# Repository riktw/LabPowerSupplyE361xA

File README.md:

# LabPowerSupplyE361xA
A E3611A based lab power supply with digital controls

More info on the corresponding [blog post.](https://justanotherelectronicsblog.com/?p=846)

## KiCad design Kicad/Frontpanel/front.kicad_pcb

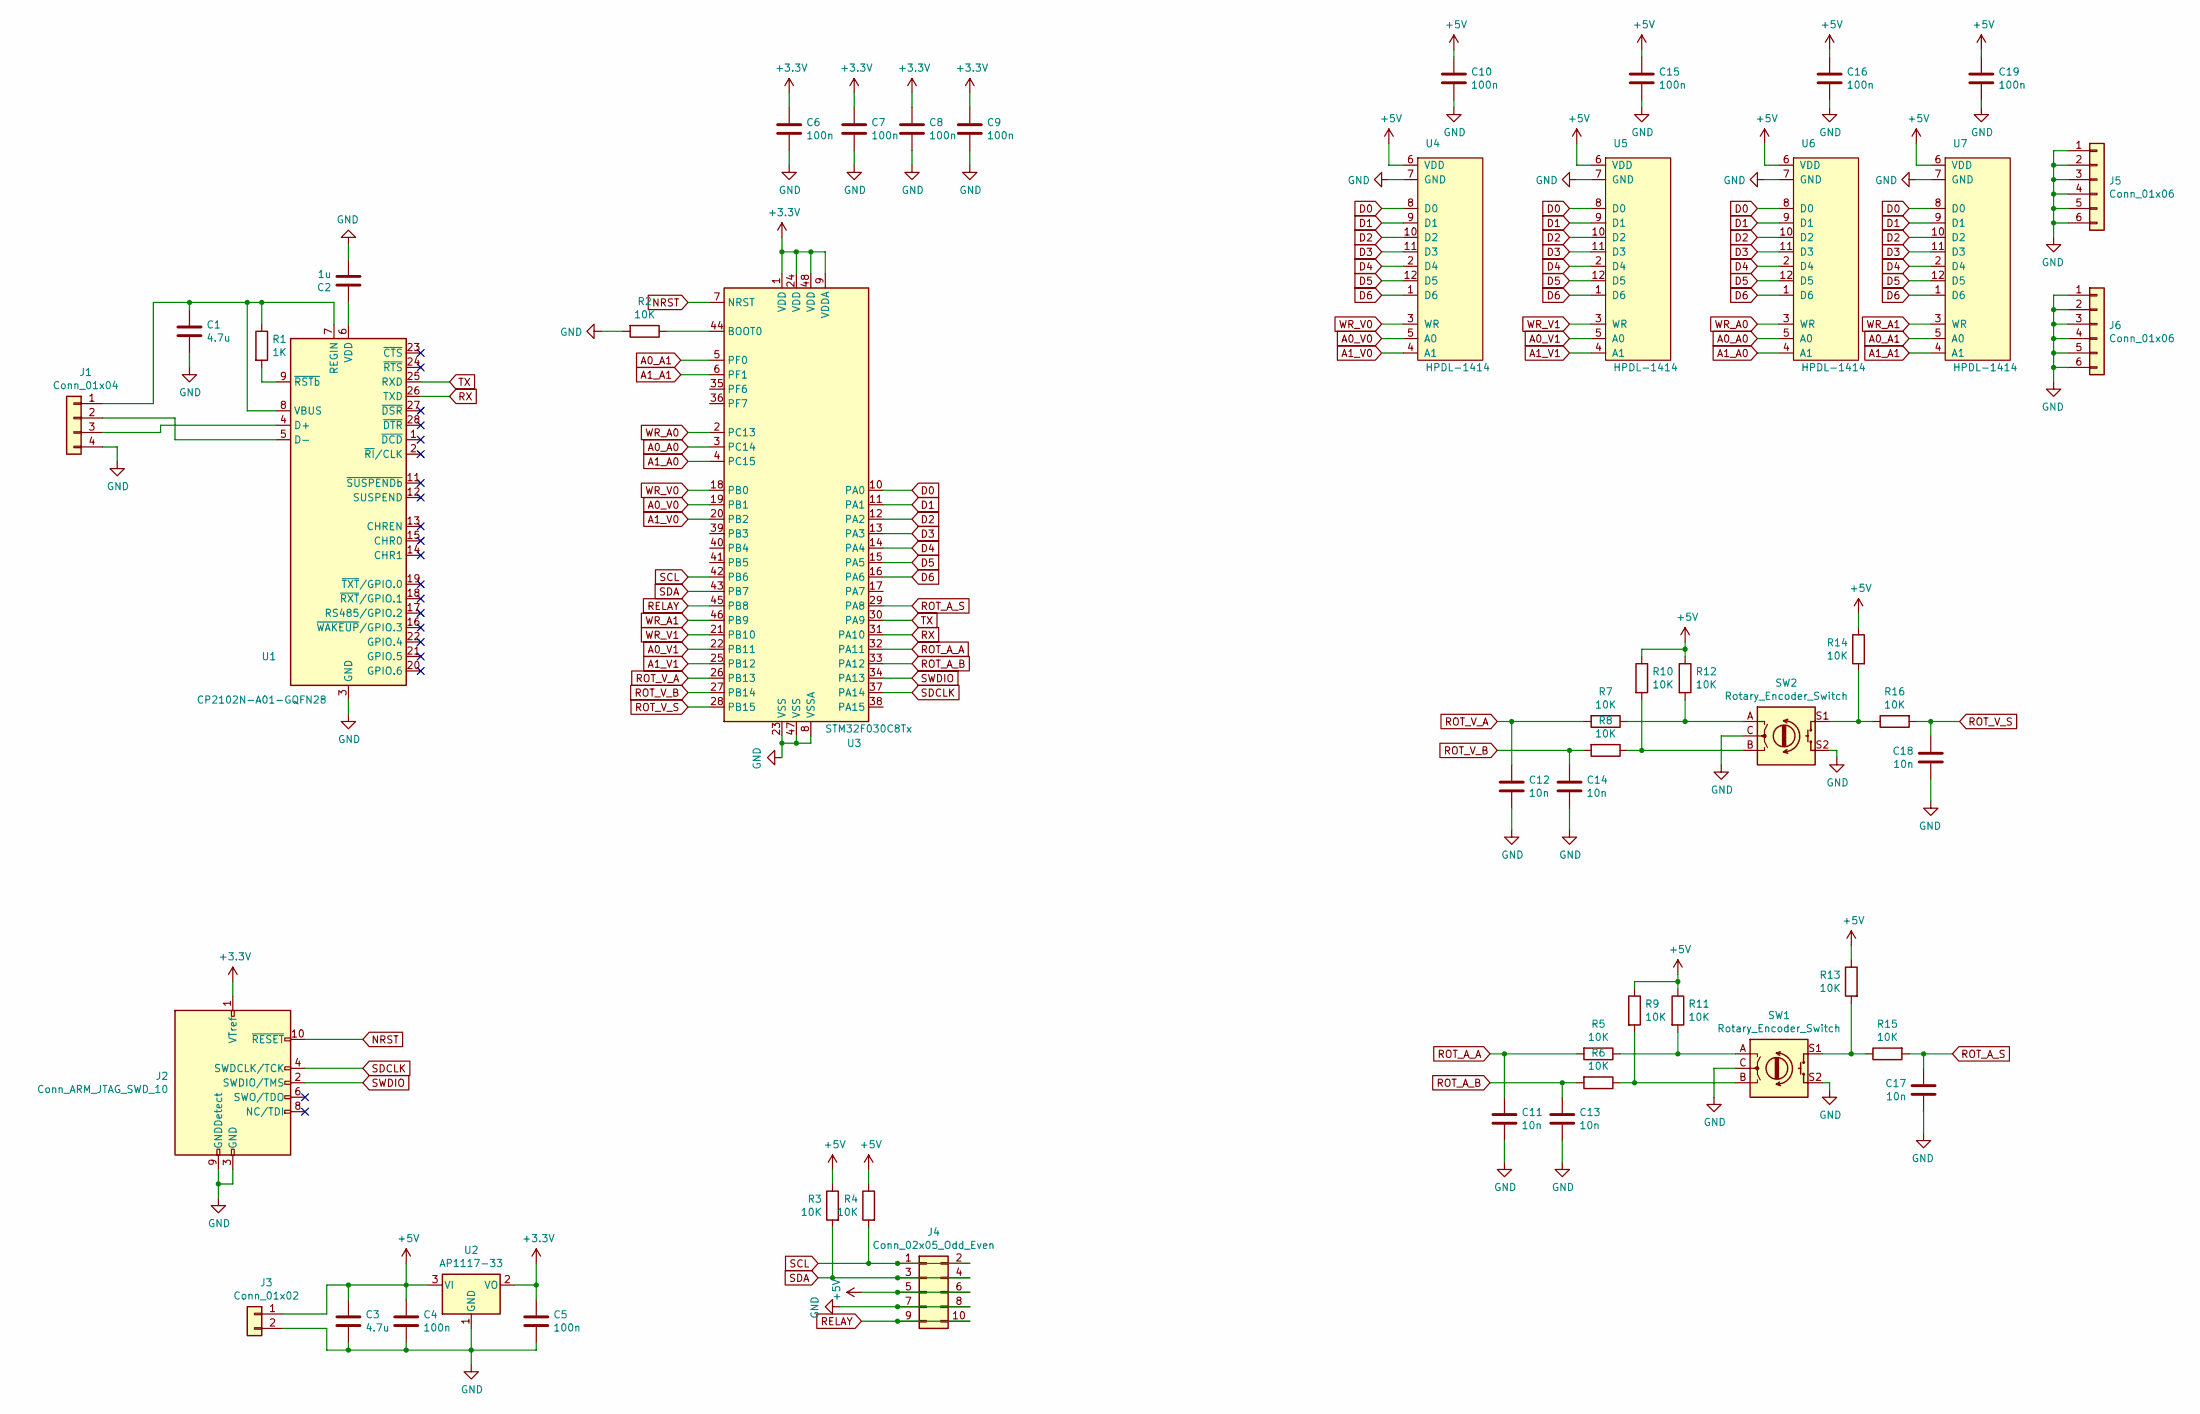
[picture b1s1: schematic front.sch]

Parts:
C1, C3: 4.7u; C_0603_1608Metric_Pad1.05x0.95mm_HandSolder
C2: 1u; C_0603_1608Metric_Pad1.05x0.95mm_HandSolder
C4, C5, C6, C7, C8, C9, C10, C15, C16, C19: 100n; C_0603_1608Metric_Pad1.05x0.95mm_HandSolder
C11, C12, C13, C14, C17, C18: 10n; C_0603_1608Metric_Pad1.05x0.95mm_HandSolder
J1: Conn_01x04; PinHeader_1x04_P2.54mm_Vertical
J2: Conn_ARM_JTAG_SWD_10; PinHeader_2x05_P1.27mm_Vertical_SMD
J3: Conn_01x02; Wago_734-132_1x02_P3.50mm_Vertical
J4: Conn_02x05_Odd_Even; IDC-Header_2x05_P2.54mm_Vertical
J5, J6: Conn_01x06; PinSocket_1x06_P2.54mm_Vertical
R1: 1K; R_0603_1608Metric_Pad1.05x0.95mm_HandSolder
R2, R3, R4, R5, R6, R7, R8, R9, R10, R11, R12, R13, R14, R15, R16: 10K; R_0603_1608Metric_Pad1.05x0.95mm_HandSolder
SW1, SW2: Rotary_Encoder_Switch; RotaryEncoder_Alps_EC11E-Switch_Vertical_H20mm
U1: CP2102N-A01-GQFN28; QFN-28-1EP_5x5mm_P0.5mm_EP3.35x3.35mm; JLC C6568
U2: AP1117-33; SOT-223-3_TabPin2
U3: STM32F030C8Tx; LQFP-48_7x7mm_P0.5mm
U4, U5, U6, U7: HPDL-1414

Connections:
+3V3: C5.1, C6.1, C7.1, C8.1, C9.1, J2.1 (VTref), U2.2 (VO), U3.1 (VDD), U3.9 (VDDA), U3.24 (VDD), U3.48 (VDD)
+5V: C3.1, C4.1, C10.1, C15.1, C16.1, C19.1, J3.1, J4.5, J4.6, R3.1, R4.1, R9.1, R10.1, R11.1, R12.1, R13.1, R14.1, U2.3 (VI), U4.6 (VDD), U5.6 (VDD), U6.6 (VDD), U7.6 (VDD)
A0_A0: U3.3 (PC14), U6.5 (A0)
A0_A1: U3.5 (PF0), U7.5 (A0)
A0_V0: U3.19 (PB1), U4.5 (A0)
A0_V1: U3.22 (PB11), U5.5 (A0)
A1_A0: U3.4 (PC15), U6.4 (A1)
A1_A1: U3.6 (PF1), U7.4 (A1)
A1_V0: U3.20 (PB2), U4.4 (A1)
A1_V1: U3.25 (PB12), U5.4 (A1)
D0: U3.10 (PA0), U4.8 (D0), U5.8 (D0), U6.8 (D0), U7.8 (D0)
D1: U3.11 (PA1), U4.9 (D1), U5.9 (D1), U6.9 (D1), U7.9 (D1)
D2: U3.12 (PA2), U4.10 (D2), U5.10 (D2), U6.10 (D2), U7.10 (D2)
D3: U3.13 (PA3), U4.11 (D3), U5.11 (D3), U6.11 (D3), U7.11 (D3)
D4: U3.14 (PA4), U4.2 (D4), U5.2 (D4), U6.2 (D4), U7.2 (D4)
D5: U3.15 (PA5), U4.12 (D5), U5.12 (D5), U6.12 (D5), U7.12 (D5)
D6: U3.16 (PA6), U4.1 (D6), U5.1 (D6), U6.1 (D6), U7.1 (D6)
GND: C1.2, C2.2, C3.2, C4.2, C5.2, C6.2, C7.2, C8.2, C9.2, C10.2, C11.2, C12.2, C13.2, C14.2, C15.2, C16.2, C17.2, C18.2, C19.2, J1.4, J2.3 (GND), J2.5 (GND), J2.9 (GNDDetect), J3.2, J4.7, J4.8, J5.1, J5.2, J5.3, J5.4, J5.5, J5.6, J6.1, J6.2, J6.3, J6.4, J6.5, J6.6, R2.2, SW1.C, SW1.S2, SW2.C, SW2.S2, U1.3 (GND), U1.29 (GND), U2.1 (GND), U3.8 (VSSA), U3.23 (VSS), U3.47 (VSS), U4.7 (GND), U5.7 (GND), U6.7 (GND), U7.7 (GND)
NRST: J2.10 (~RESET~), U3.7 (NRST)
unnamed: C1.1, J1.1, R1.1, U1.7 (REGIN), U1.8 (VBUS)
unnamed: C2.1, U1.6 (VDD)
unnamed: J1.2, U1.5 (D-)
unnamed: J1.3, U1.4 (D+)
unnamed: R1.2, U1.9 (~RSTb)
unnamed: R2.1, U3.44 (BOOT0)
unnamed: R6.1, R9.2, SW1.B
unnamed: R8.1, R10.2, SW2.B
unnamed: R5.1, R11.2, SW1.A
unnamed: R7.1, R12.2, SW2.A
unnamed: R13.2, R15.1, SW1.S1
unnamed: R14.2, R16.1, SW2.S1
RELAY: J4.9, J4.10, U3.45 (PB8)
ROT_A_A: C11.1, R5.2, U3.32 (PA11)
ROT_A_B: C13.1, R6.2, U3.33 (PA12)
ROT_A_S: C17.1, R15.2, U3.29 (PA8)
ROT_V_A: C12.1, R7.2, U3.26 (PB13)
ROT_V_B: C14.1, R8.2, U3.27 (PB14)
ROT_V_S: C18.1, R16.2, U3.28 (PB15)
RX: U1.26 (TXD), U3.31 (PA10)
SCL: J4.1, J4.2, R4.2, U3.42 (PB6)
SDA: J4.3, J4.4, R3.2, U3.43 (PB7)
SDCLK: J2.4 (SWDCLK/TCK), U3.37 (PA14)
SWDIO: J2.2 (SWDIO/TMS), U3.34 (PA13)
TX: U1.25 (RXD), U3.30 (PA9)
WR_A0: U3.2 (PC13), U6.3 (WR)
WR_A1: U3.46 (PB9), U7.3 (WR)
WR_V0: U3.18 (PB0), U4.3 (WR)
WR_V1: U3.21 (PB10), U5.3 (WR)

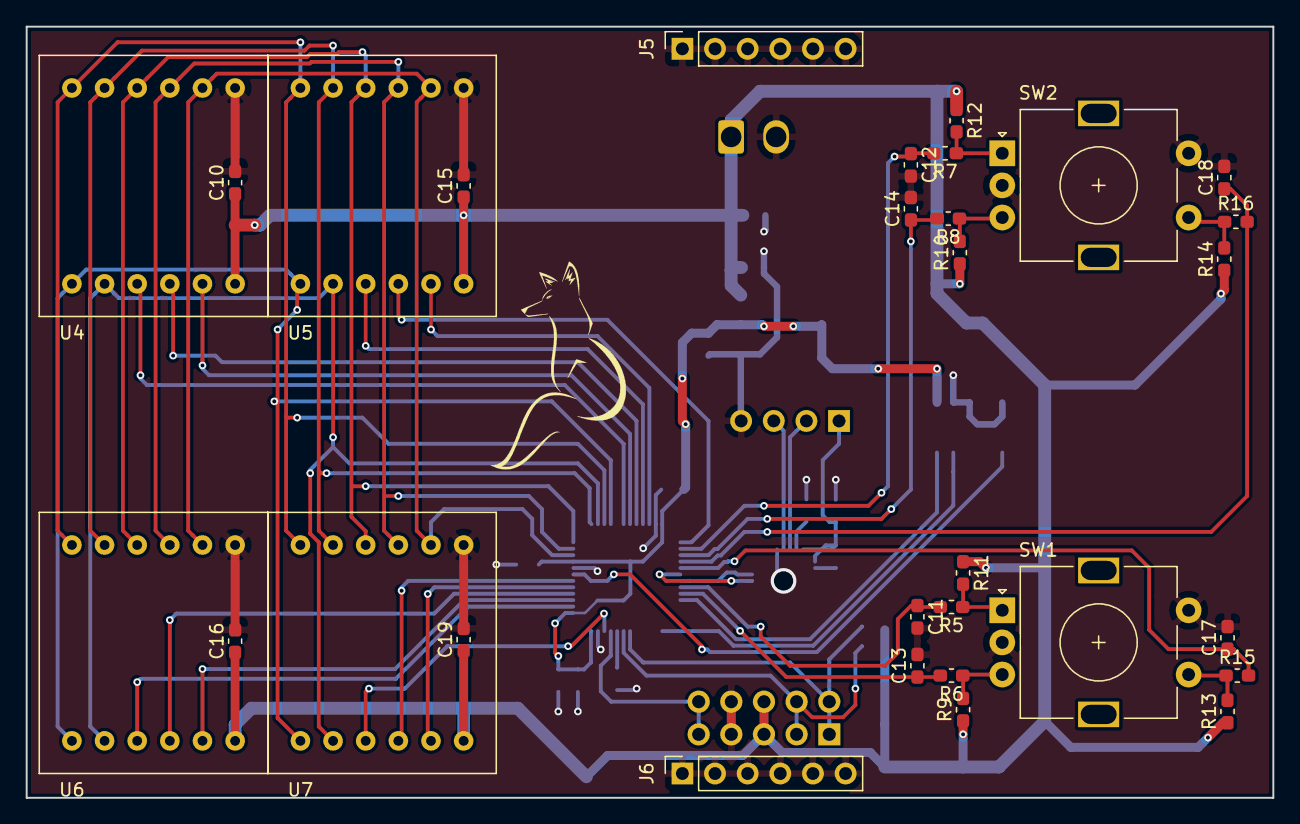
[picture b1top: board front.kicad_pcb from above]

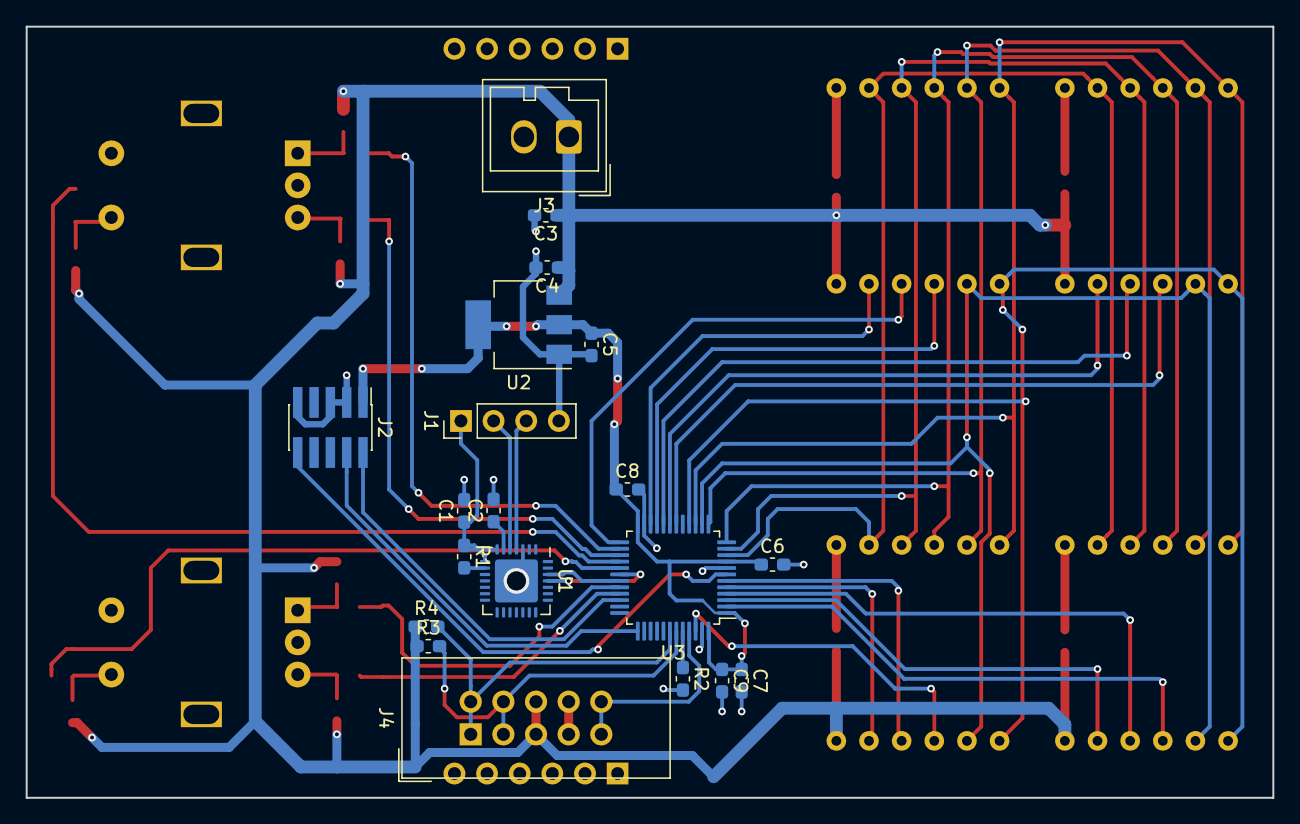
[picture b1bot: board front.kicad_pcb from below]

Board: 2 copper layers, 97.0 x 60.0 mm, 50 parts (20 on the bottom side), 48 nets.

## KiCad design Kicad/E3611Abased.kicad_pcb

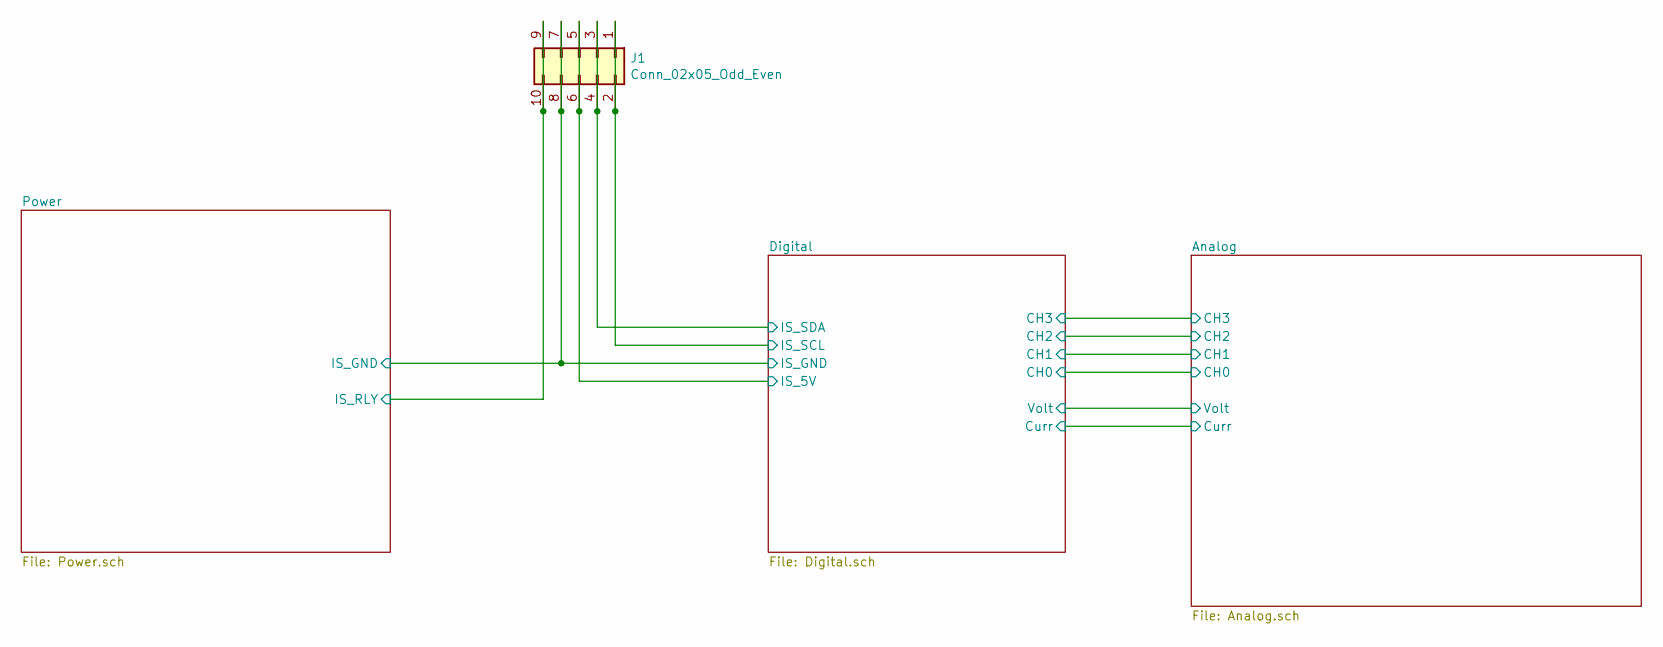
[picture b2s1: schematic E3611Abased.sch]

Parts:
J1: Conn_02x05_Odd_Even; IDC-Header_2x05_P2.54mm_Vertical

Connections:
/Digital/IS_5V: J1.5, J1.6; also elsewhere on the board
/Digital/IS_GND: J1.7, J1.8; also elsewhere on the board
/Digital/IS_SCL: J1.1, J1.2; also elsewhere on the board
/Digital/IS_SDA: J1.3, J1.4; also elsewhere on the board
/Power/IS_RLY: J1.9, J1.10; also elsewhere on the board

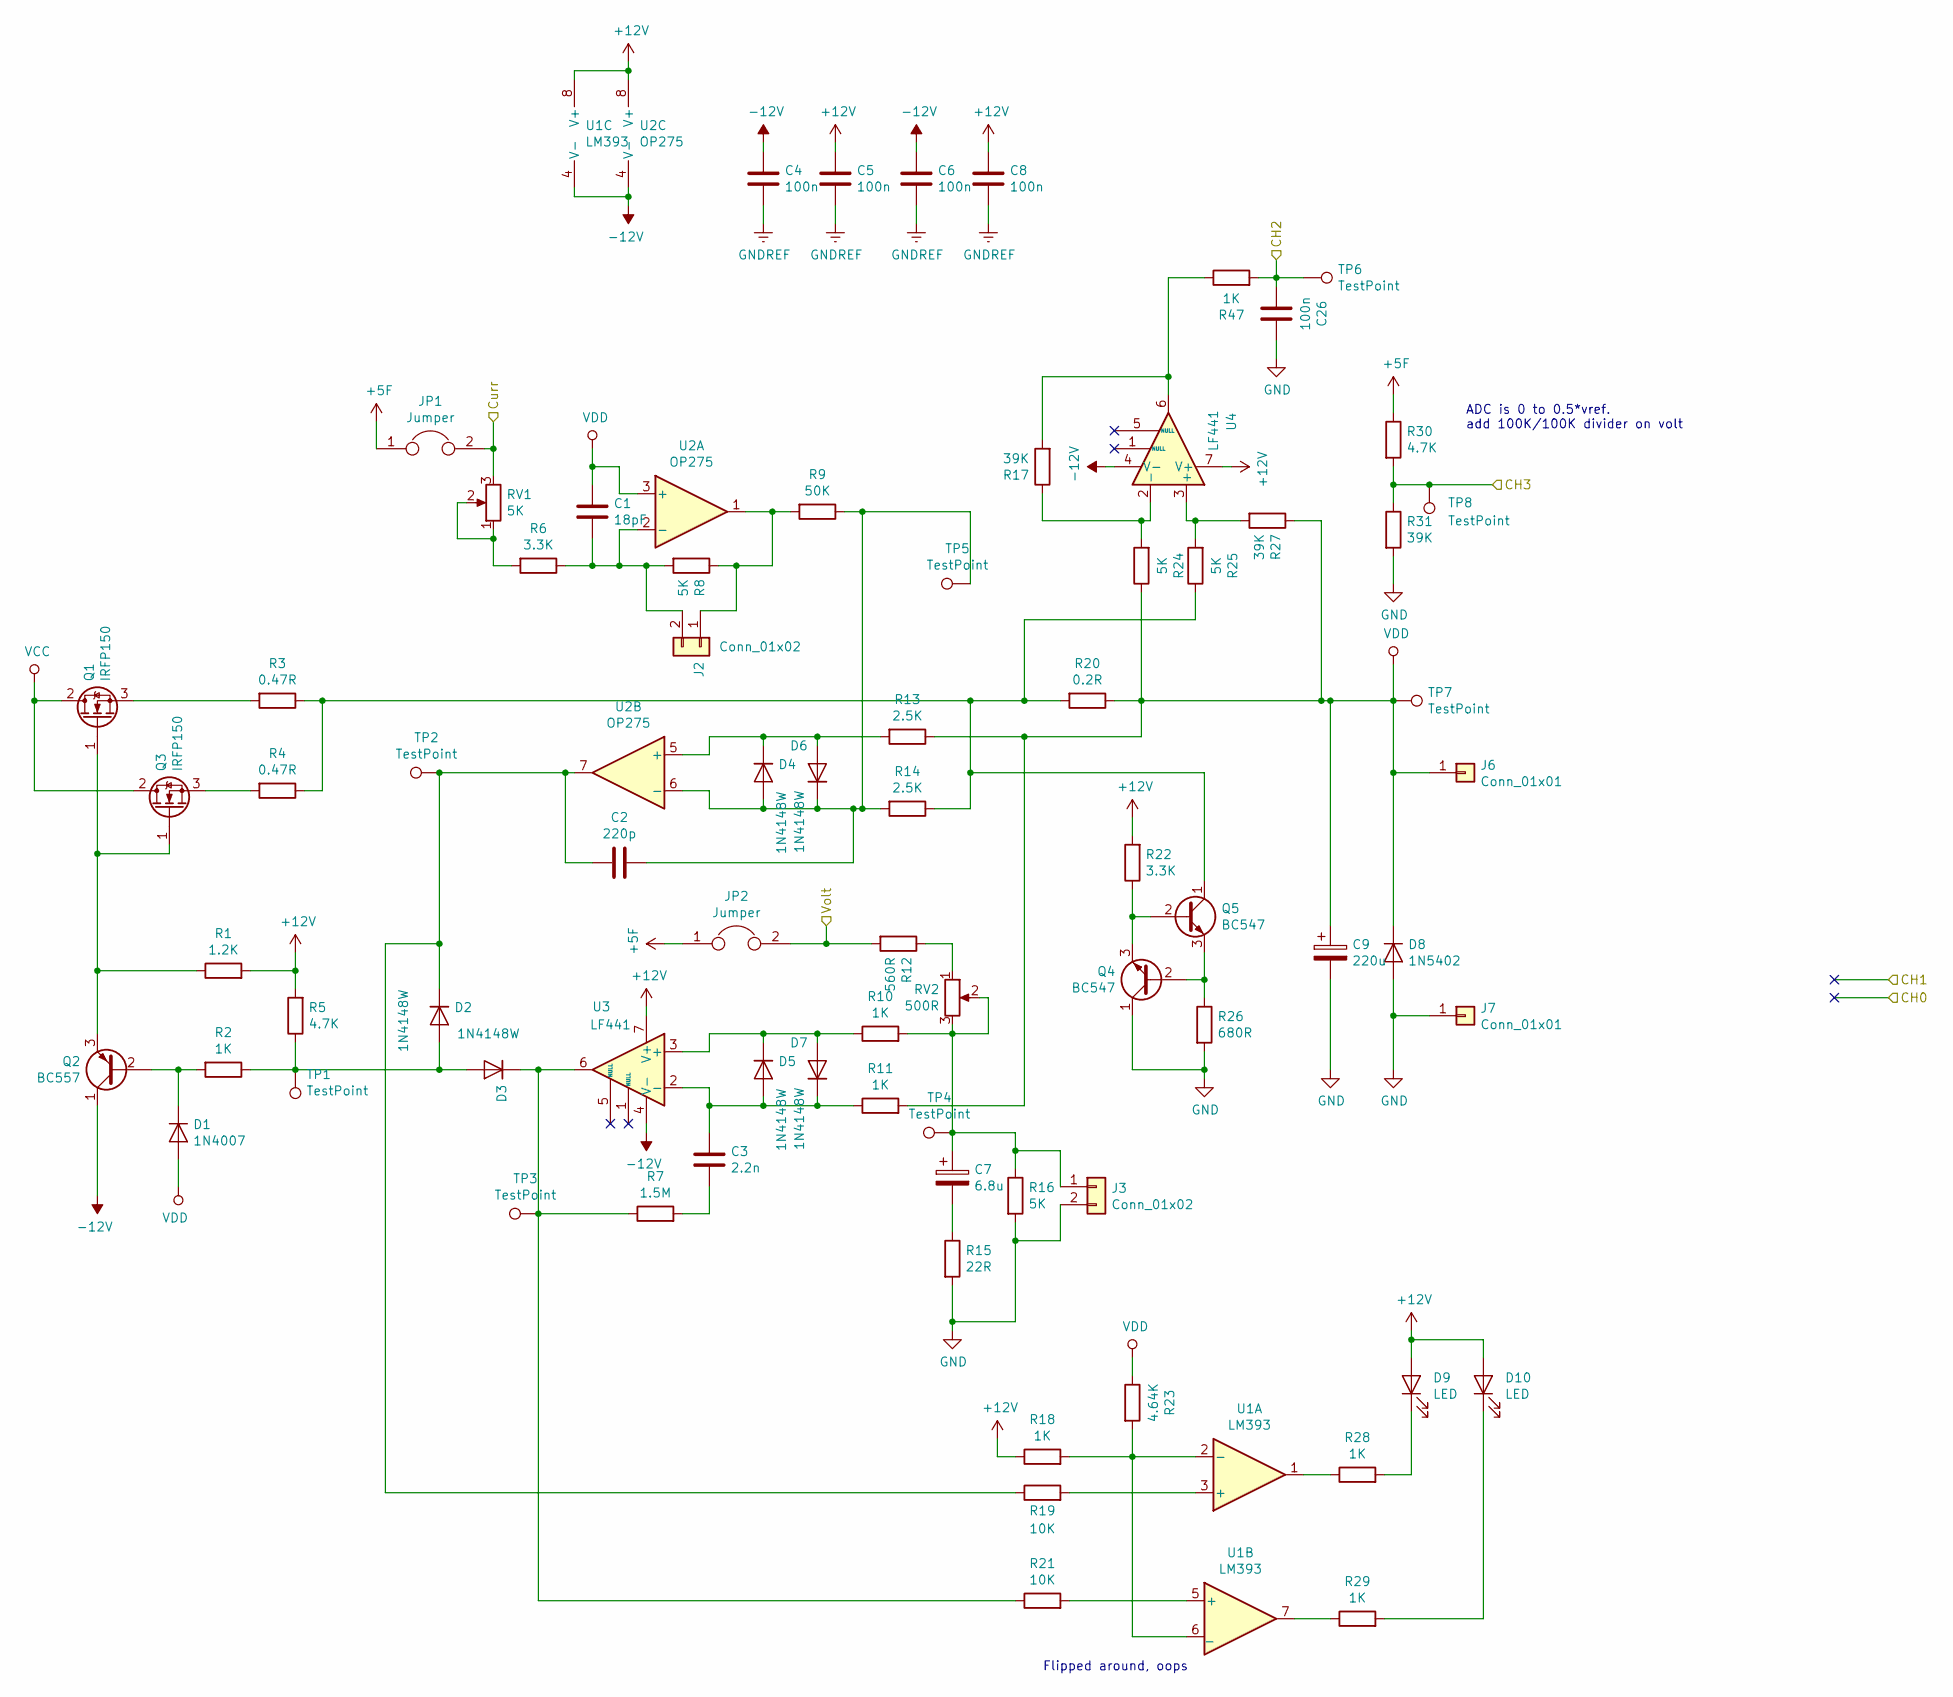
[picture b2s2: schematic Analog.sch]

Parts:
C1: 18pF; C_0603_1608Metric_Pad1.05x0.95mm_HandSolder
C2: 220p; C_0603_1608Metric_Pad1.05x0.95mm_HandSolder
C3: 2.2n; C_0603_1608Metric_Pad1.05x0.95mm_HandSolder
C4, C5, C6, C8, C26: 100n; C_0603_1608Metric_Pad1.05x0.95mm_HandSolder
C7: 6.8u; CP_Elec_6.3x3
C9: 220u; CP_Radial_D10.0mm_P5.00mm
D1: 1N4007; D_DO-41_SOD81_P10.16mm_Horizontal
D2, D3, D4, D5, D6, D7: 1N4148W; D_SOD-123
D8: 1N5402; D_DO-201AD_P15.24mm_Horizontal
D9, D10: LED; LED_D5.0mm
J2, J3: Conn_01x02; TerminalBlock_Phoenix_MKDS-1,5-2-5.08_1x02_P5.08mm_Horizont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
J6, J7: Conn_01x01; 24.243_Banana_plug
JP1, JP2: Jumper; SolderJumper-2_P1.3mm_Open_Pad1.0x1.5mm
Q1, Q3: IRFP150; TO-247-3_Vertical
Q2: BC557; TO-92_Inline
Q4, Q5: BC547; TO-92_Inline
R1: 1.2K; R_0603_1608Metric_Pad1.05x0.95mm_HandSolder
R2, R10, R11, R18, R28, R29, R47: 1K; R_0603_1608Metric_Pad1.05x0.95mm_HandSolder
R3, R4: 0.47R; R_Axial_DIN0207_L6.3mm_D2.5mm_P15.24mm_Horizontal
R5, R30: 4.7K; R_0603_1608Metric_Pad1.05x0.95mm_HandSolder
R6, R22: 3.3K; R_0603_1608Metric_Pad1.05x0.95mm_HandSolder
R7: 1.5M; R_0603_1608Metric_Pad1.05x0.95mm_HandSolder
R8, R16, R24, R25: 5K; R_0603_1608Metric_Pad1.05x0.95mm_HandSolder
R9: 50K; R_0603_1608Metric_Pad1.05x0.95mm_HandSolder
R12: 560R; R_0603_1608Metric_Pad1.05x0.95mm_HandSolder
R13, R14: 2.5K; R_0603_1608Metric_Pad1.05x0.95mm_HandSolder
R15: 22R; R_0603_1608Metric_Pad1.05x0.95mm_HandSolder
R17, R27, R31: 39K; R_0603_1608Metric_Pad1.05x0.95mm_HandSolder
R19, R21: 10K; R_0603_1608Metric_Pad1.05x0.95mm_HandSolder
R20: 0.2R; R_Axial_DIN0207_L6.3mm_D2.5mm_P15.24mm_Horizontal
R23: 4.64K; R_0603_1608Metric_Pad1.05x0.95mm_HandSolder
R26: 680R; R_0603_1608Metric_Pad1.05x0.95mm_HandSolder
RV1: 5K; Potentiometer_Bourns_3266Y_Vertical
RV2: 500R; Potentiometer_Bourns_3266Y_Vertical
TP1, TP2, TP3, TP4, TP5, TP6, TP7, TP8: TestPoint; TestPoint_Loop_D1.80mm_Drill1.0mm_Beaded
U1: LM393; SOIC-8_3.9x4.9mm_P1.27mm
U2: OP275; SOIC-8_3.9x4.9mm_P1.27mm
U3, U4: LF441; SOIC-8_3.9x4.9mm_P1.27mm

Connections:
+5F: JP1.1, JP2.1, R30.1; also elsewhere on the board
+12V: C5.1, C8.1, D9.2 (A), D10.2 (A), R1.2, R5.2, R18.1, R22.2, U1.8 (V+), U2.8 (V+), U3.7 (V+), U4.7 (V+); also elsewhere on the board
-12V: C4.1, C6.1, Q2.1 (C), U1.4 (V-), U2.4 (V-), U3.4 (V-), U4.4 (V-); also elsewhere on the board
/Analog/CH2: C26.2, R47.2, TP6.1; also elsewhere on the board
/Analog/CH3: R30.2, R31.1, TP8.1; also elsewhere on the board
/Analog/Curr: JP1.2, RV1.3; also elsewhere on the board
/Analog/Volt: JP2.2, R12.2; also elsewhere on the board
GND: C9.2, C26.1, D8.2 (A), J3.2, J7.1, Q4.1 (C), R15.2, R16.2, R26.2, R31.2; also elsewhere on the board
GNDREF: C1.1, C4.2, C5.2, C6.2, C8.2, C9.1, D1.2 (A), D8.1 (K), J6.1, R11.2, R13.1, R20.1, R23.1, R24.1, R27.1, TP7.1, U2.3 (+); also elsewhere on the board
unnamed: C1.2, J2.2, R6.1, R8.2, U2.2 (-)
unnamed: C2.1, D4.2 (A), D6.1 (K), R9.1, R14.2, TP5.1, U2.6 (-)
unnamed: C2.2, D2.1 (K), R19.1, TP2.1, U2.7
unnamed: C3.1, D5.2 (A), D7.1 (K), R11.1, U3.2 (-)
unnamed: C3.2, R7.2
unnamed: C7.1, J3.1, R10.2, R16.1, RV2.2, RV2.3, TP4.1
unnamed: C7.2, R15.1
unnamed: D1.1 (K), Q2.2 (B), R2.2
unnamed: D2.2 (A), D3.2 (A), R2.1, R5.1, TP1.1
unnamed: D3.1 (K), R7.1, R21.1, TP3.1, U3.6
unnamed: D4.1 (K), D6.2 (A), R13.2, U2.5 (+)
unnamed: D5.1 (K), D7.2 (A), R10.1, U3.3 (+)
unnamed: D9.1 (K), R28.2
unnamed: D10.1 (K), R29.2
unnamed: J2.1, R8.1, R9.2, U2.1
unnamed: Q1.1 (G), Q2.3 (E), Q3.1 (G), R1.1
unnamed: Q1.3 (S), R3.2
unnamed: Q3.3 (S), R4.2
unnamed: Q4.2 (B), Q5.3 (E), R26.1
unnamed: Q4.3 (E), Q5.2 (B), R22.1
unnamed: Q5.1 (C), R3.1, R4.1, R14.1, R20.2, R25.1
unnamed: R6.2, RV1.1, RV1.2
unnamed: R12.1, RV2.1
unnamed: R17.1, R24.2, U4.2 (-)
unnamed: R17.2, R47.1, U4.6
unnamed: R18.2, R23.2, U1.2 (-), U1.6 (_)
unnamed: R19.2, U1.3 (+)
unnamed: R21.2, U1.5 (+)
unnamed: R25.2, R27.2, U4.3 (+)
unnamed: R28.1, U1.1
unnamed: R29.1, U1.7
VCC: Q1.2 (D), Q3.2 (D); also elsewhere on the board

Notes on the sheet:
ADC is 0 to 0.5*vref. add 100K/100K divider on volt
Flipped around, oops

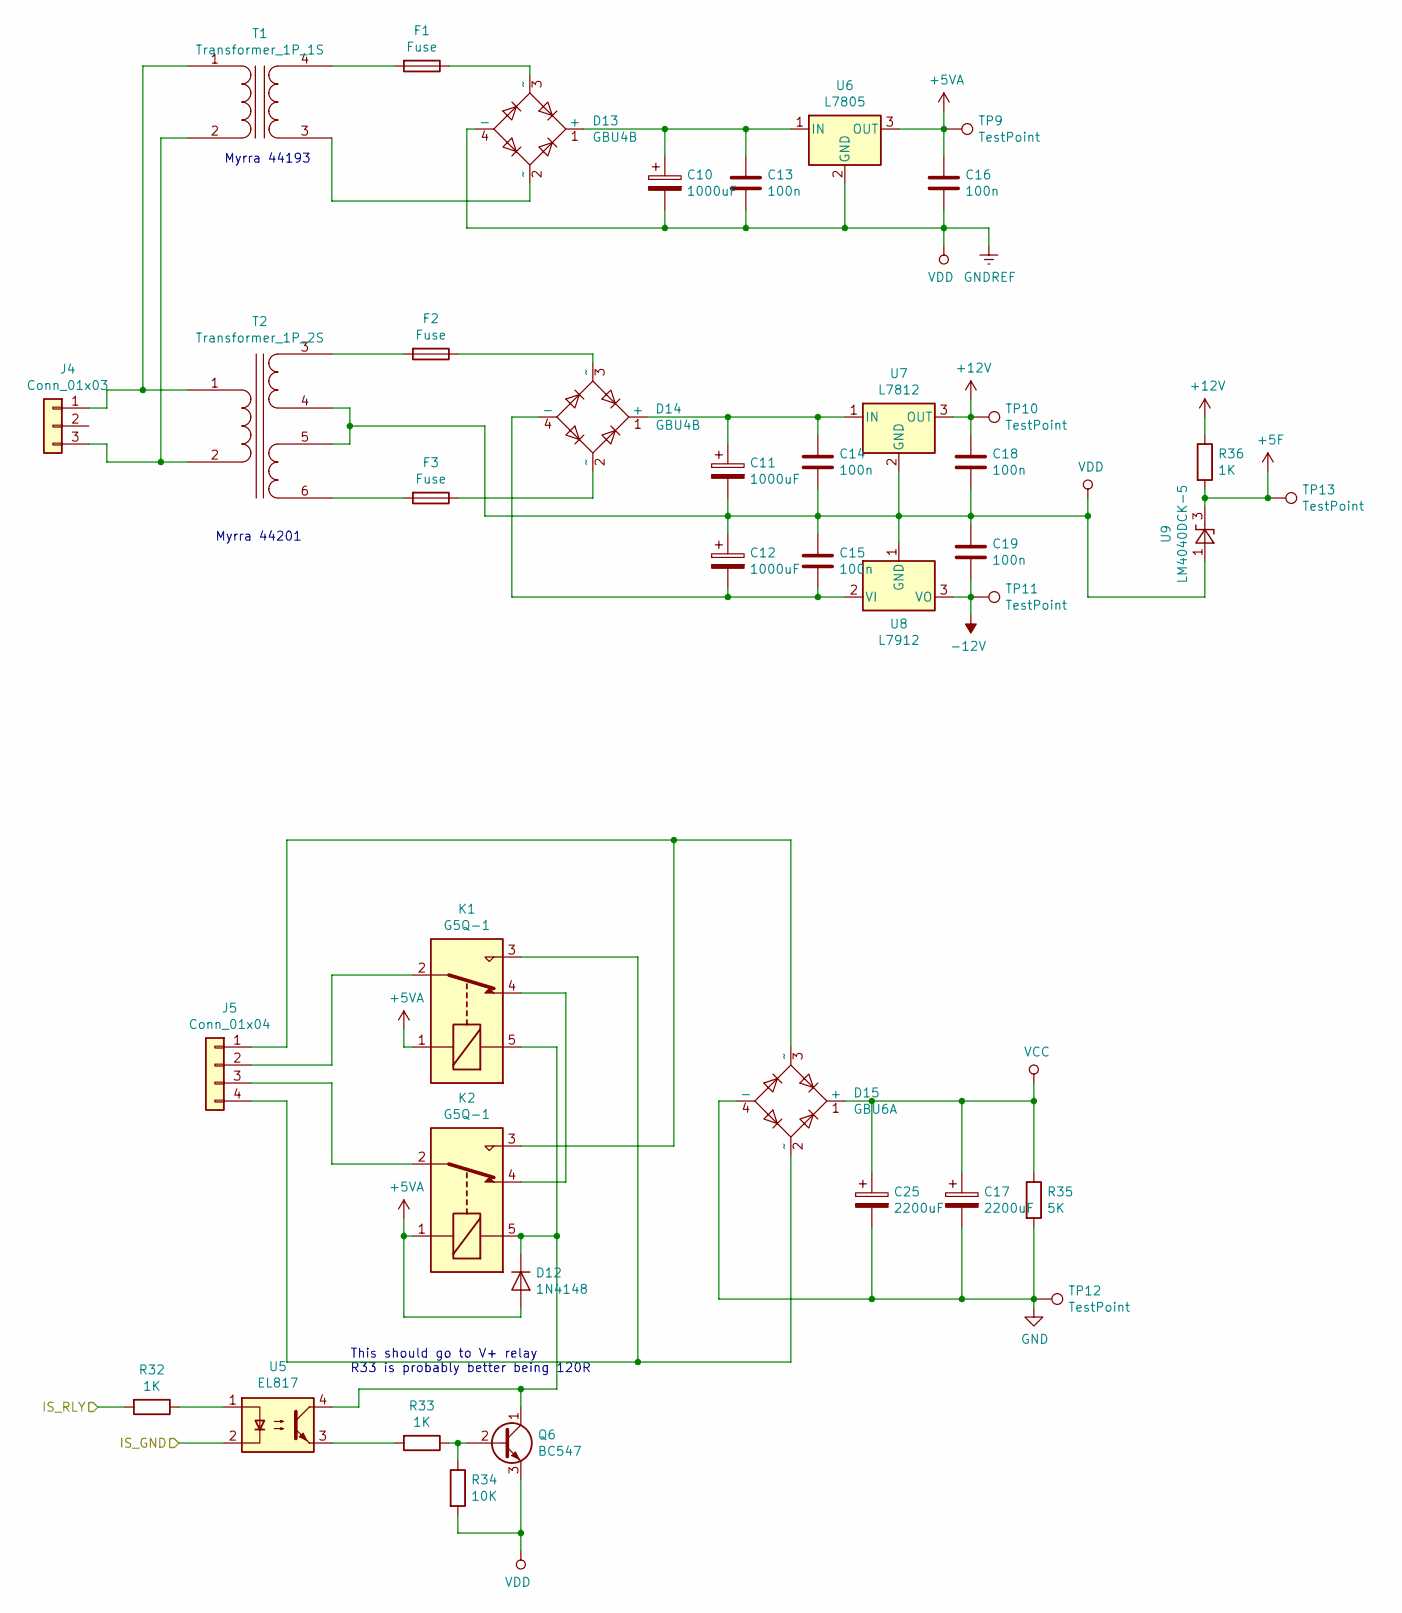
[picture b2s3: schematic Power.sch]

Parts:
C10, C11, C12: 1000uF; CP_Radial_D10.0mm_P5.00mm
C13, C14, C15, C16, C18, C19: 100n; C_Disc_D5.0mm_W2.5mm_P5.00mm
C17, C25: 2200uF; CP_Radial_D18.0mm_P7.50mm
D12: 1N4148; D_DO-35_SOD27_P7.62mm_Horizontal
D13, D14: GBU4B; Diode_Bridge_Vishay_GBU
D15: GBU6A; Diode_Bridge_Vishay_GBU
F1, F2, F3: Fuse; Fuseholder_Cylinder-5x20mm_Stelvio-Kontek_PTF78_Horizontal_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
J4: Conn_01x03; TerminalBlock_Phoenix_MKDS-1,5-3-5.08_1x03_P5.08mm_Horizont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
J5: Conn_01x04; TerminalBlock_Phoenix_MKDS-1,5-4-5.08_1x04_P5.08mm_Horizont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
K1, K2: G5Q-1; Relay_SPDT_Omron-G5Q-1
Q6: BC547; TO-92_Inline
R32, R33: 1K; R_0603_1608Metric_Pad1.05x0.95mm_HandSolder
R34: 10K; R_0603_1608Metric_Pad1.05x0.95mm_HandSolder
R35: 5K; R_Axial_DIN0414_L11.9mm_D4.5mm_P15.24mm_Horizontal
R36: 1K; R_0603_1608Metric
T1: Transformer_1P_1S; 44XXX_Transformer_3.2VA_Single
T2: Transformer_1P_2S; 44XXX_Transformer_3.2VA
TP9, TP10, TP11, TP12, TP13: TestPoint; TestPoint_Loop_D1.80mm_Drill1.0mm_Beaded
U5: EL817; DIP-4_W7.62mm
U6: L7805; TO-220-3_Vertical
U7: L7812; TO-220-3_Vertical
U8: L7912; TO-220-3_Vertical
U9: LM4040DCK-5; SOT-353_SC-70-5

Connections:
+5F: R36.2, TP13.1, U9.3 (K); also elsewhere on the board
+5VA: C16.1, D12.2 (A), K1.1, K2.1, TP9.1, U6.3 (OUT); also elsewhere on the board
+12V: C18.1, R36.1, TP10.1, U7.3 (OUT); also elsewhere on the board
-12V: C19.2, TP11.1, U8.3 (VO); also elsewhere on the board
/Digital/IS_GND: U5.2; also elsewhere on the board
/Power/IS_RLY: R32.2; also elsewhere on the board
GND: C17.2, C25.2, D15.4 (-), R35.2, TP12.1; also elsewhere on the board
GNDREF: C10.2, C11.2, C12.1, C13.2, C14.2, C15.1, C16.2, C18.2, C19.1, D13.4 (-), Q6.3 (E), R34.2, T2.4 (SB), T2.5 (SC), U6.2 (GND), U7.2 (GND), U8.1 (GND), U9.1 (A); also elsewhere on the board
unnamed: C10.1, C13.1, D13.1 (+), U6.1 (IN)
unnamed: C11.1, C14.1, D14.1 (+), U7.1 (IN)
unnamed: C12.2, C15.2, D14.4 (-), U8.2 (VI)
unnamed: D12.1 (K), K1.5, K2.5, Q6.1 (C), U5.4
unnamed: D13.2 (~~), T1.3 (SA)
unnamed: D13.3 (~~), F1.1
unnamed: D14.2 (~~), F3.1
unnamed: D14.3 (~~), F2.1
unnamed: D15.2 (~~), J5.4, K1.3
unnamed: D15.3 (~~), J5.1, K2.3
unnamed: F1.2, T1.4 (SB)
unnamed: F2.2, T2.3 (SA)
unnamed: F3.2, T2.6 (SD)
unnamed: J4.1, T1.1 (AA), T2.1 (AA)
unnamed: J4.3, T1.2 (AB), T2.2 (AB)
unnamed: J5.2, K1.2
unnamed: J5.3, K2.2
unnamed: K1.4, K2.4
unnamed: Q6.2 (B), R33.1, R34.1
unnamed: R32.1, U5.1
unnamed: R33.2, U5.3
VCC: C17.1, C25.1, D15.1 (+), R35.1; also elsewhere on the board

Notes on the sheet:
Myrra 44201
Myrra 44193
This should go to V+ relay R33 is probably better being 120R

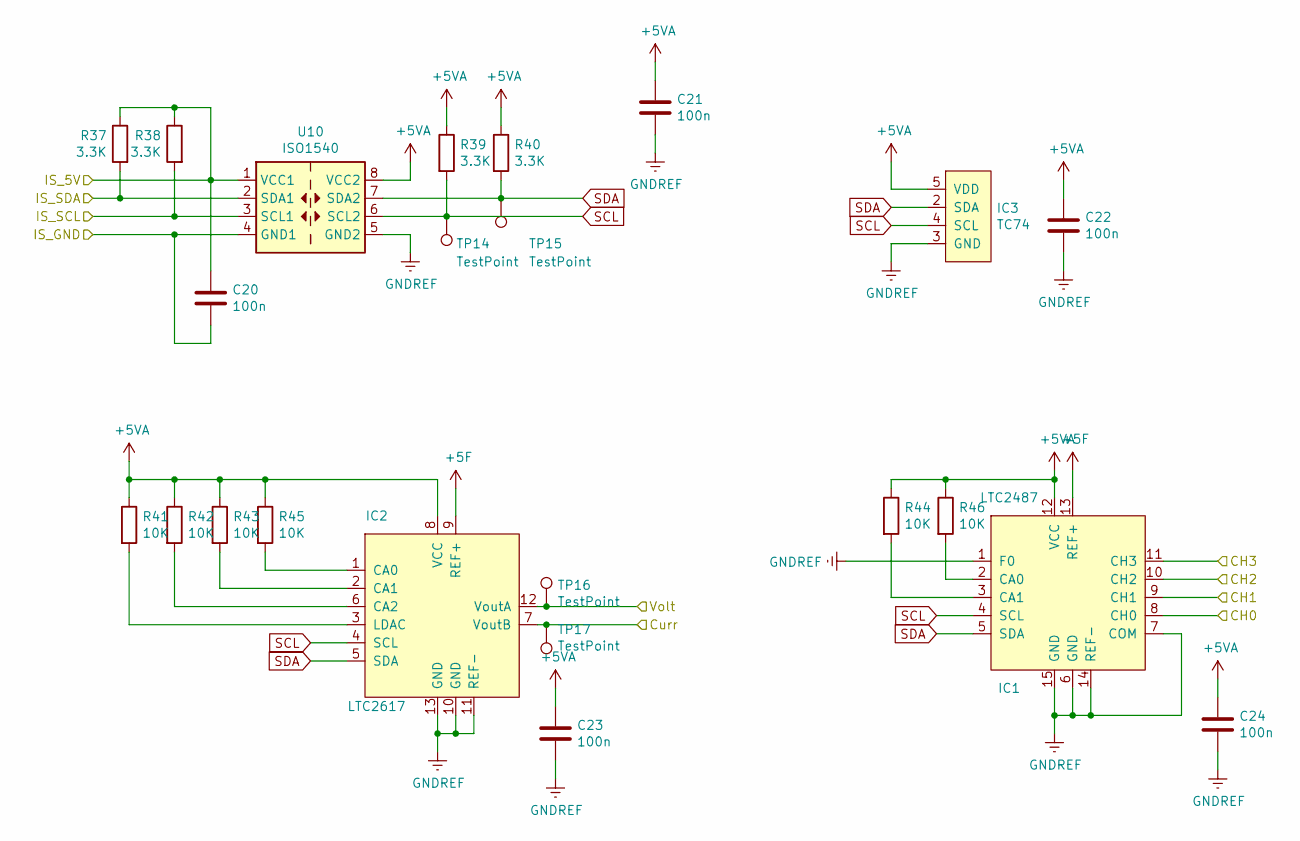
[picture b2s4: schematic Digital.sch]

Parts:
C20, C21, C22, C23, C24: 100n; C_0603_1608Metric_Pad1.05x0.95mm_HandSolder
IC1: LTC2487; DFN-14-1EP_3x4mm_P0.5mm_EP1.7x3.3mm
IC2: LTC2617; DFN-12-1EP_3x4mm_P0.5mm_EP1.7x3.3mm
IC3: TC74; TO-220-5_Vertical
R37, R38, R39, R40: 3.3K; R_0603_1608Metric
R41, R42, R43, R44, R45, R46: 10K; R_0603_1608Metric
TP14, TP15, TP16, TP17: TestPoint; TestPoint_Loop_D1.80mm_Drill1.0mm_Beaded
U10: ISO1540; SOIC-8_3.9x4.9mm_P1.27mm

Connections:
+5F: IC1.13 (REF+), IC2.9 (REF+); also elsewhere on the board
+5VA: C21.1, C22.1, C23.1, C24.1, IC1.12 (VCC), IC2.8 (VCC), IC3.5 (VDD), R39.1, R40.1, R41.1, R42.1, R43.1, R44.1, R45.1, R46.1, U10.8 (VCC2); also elsewhere on the board
/Analog/CH0: IC1.8 (CH0)
/Analog/CH1: IC1.9 (CH1)
/Analog/CH2: IC1.10 (CH2); also elsewhere on the board
/Analog/CH3: IC1.11 (CH3); also elsewhere on the board
/Analog/Curr: IC2.7 (VoutB), TP17.1; also elsewhere on the board
/Analog/Volt: IC2.12 (VoutA), TP16.1; also elsewhere on the board
/Digital/IS_5V: C20.1, R37.1, R38.1, U10.1 (VCC1); also elsewhere on the board
/Digital/IS_GND: C20.2, U10.4 (GND1); also elsewhere on the board
/Digital/IS_SCL: R38.2, U10.3 (SCL1); also elsewhere on the board
/Digital/IS_SDA: R37.2, U10.2 (SDA1); also elsewhere on the board
GNDREF: C21.2, C22.2, C23.2, C24.2, IC1.1 (F0), IC1.6 (GND), IC1.7 (COM), IC1.14 (REF-), IC1.15 (GND), IC2.10 (GND), IC2.11 (REF-), IC2.13 (GND), IC3.3 (GND), U10.5 (GND2); also elsewhere on the board
unnamed: IC1.2 (CA0), R46.2
unnamed: IC1.3 (CA1), R44.2
unnamed: IC2.1 (CA0), R45.2
unnamed: IC2.2 (CA1), R43.2
unnamed: IC2.3 (LDAC), R41.2
unnamed: IC2.6 (CA2), R42.2
SCL: IC1.4 (SCL), IC2.4 (SCL), IC3.4 (SCL), R39.2, TP14.1, U10.6 (SCL2)
SDA: IC1.5 (SDA), IC2.5 (SDA), IC3.2 (SDA), R40.2, TP15.1, U10.7 (SDA2)

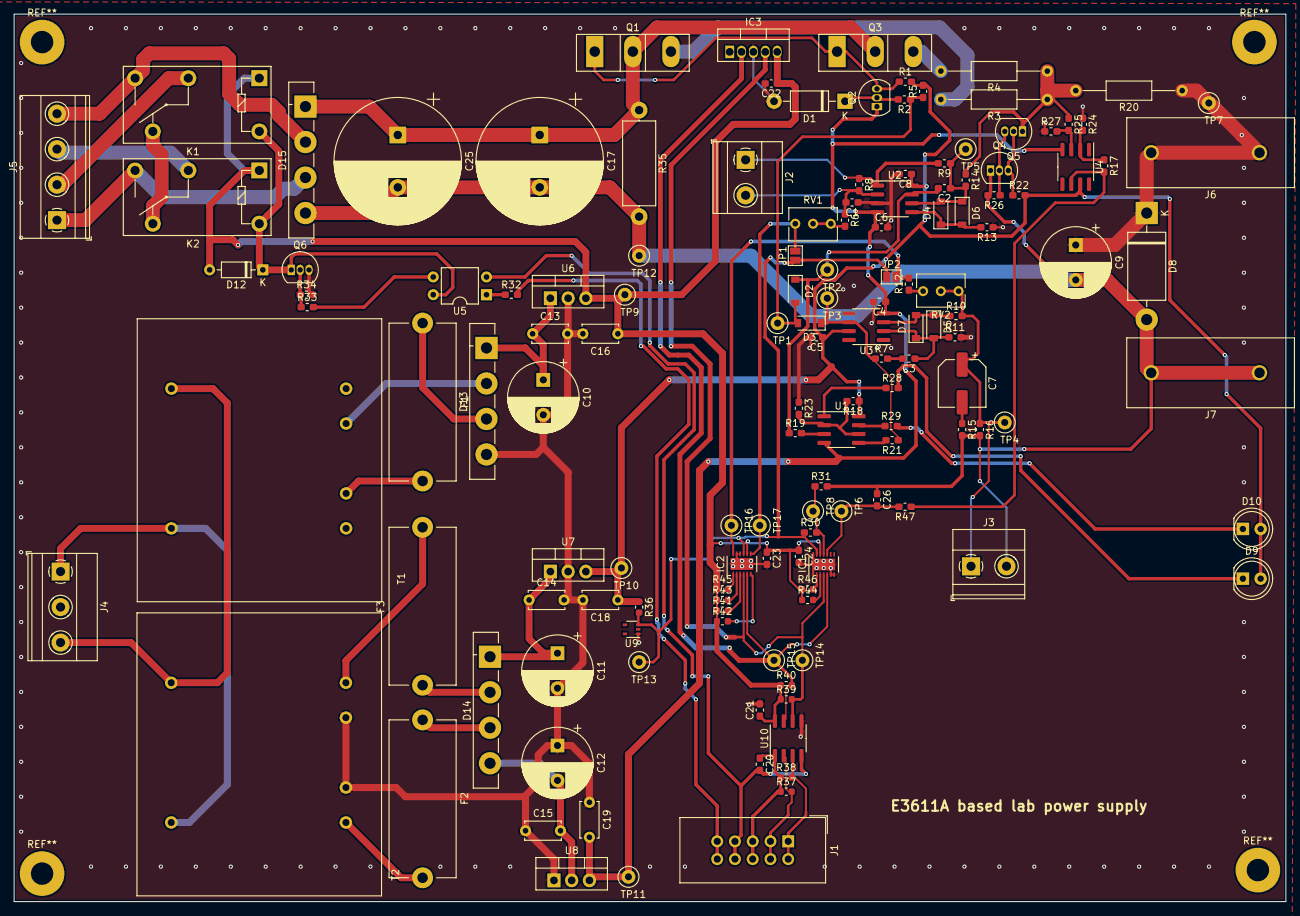
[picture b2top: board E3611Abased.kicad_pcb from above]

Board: 2 copper layers, 182.0 x 127.0 mm, 141 parts (0 on the bottom side), 76 nets.

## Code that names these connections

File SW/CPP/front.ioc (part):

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PB13.GPIOParameters=GPIO_Label,GPIO_ModeDefaultEXTI
Mcu.UserName=STM32F100C6Tx
PC13-TAMPER-RTC.GPIOParameters=GPIO_Label
PB14.GPIO_Label=ROT_V_B
PA12.GPIOParameters=GPIO_Label
PA11.GPIOParameters=GPIO_Label,GPIO_ModeDefaultEXTI
PA3.GPIOParameters=GPIO_Label
PA6.GPIO_Label=D6
PB0.GPIO_Label=WR_V0
PB13.GPIO_Label=ROT_V_A
PB11.Signal=GPIO_Output
PB13.Signal=GPXTI13
PB15.Signal=GPXTI15
PA2.GPIOParameters=GPIO_Label
PC15-OSC32_OUT.GPIO_Label=A1_A0
RCC.SYSCLKSource=RCC_SYSCLKSOURCE_PLLCLK
PD1-OSC_OUT.Signal=GPIO_Output
PD1-OSC_OUT.GPIO_Label=A1_A1
PA12.Signal=GPIO_Input
PB6.Signal=I2C1_SCL
PB6.Mode=I2C
PA8.GPIOParameters=GPIO_Label
PA0-WKUP.GPIOParameters=GPIO_Label
PB2.Signal=GPIO_Output
PB12.GPIO_Label=A1_V1
PD1-OSC_OUT.GPIOParameters=GPIO_Label
PB0.GPIOParameters=GPIO_Label
PA1.GPIOParameters=GPIO_Label
PA14.Mode=Serial_Wire
PB1.GPIO_Label=A0_V0
PB7.Signal=I2C1_SDA
PA8.Signal=GPXTI8
PC14-OSC32_IN.GPIOParameters=GPIO_Label
Mcu.Package=LQFP48
PB9.Signal=GPIO_Output
PB1.Signal=GPIO_Output
PA6.Signal=GPIO_Output
PA2.GPIO_Label=D2
PA10.Signal=USART1_RX
PA5.GPIOParameters=GPIO_Label
PB14.GPIOParameters=GPIO_Label
PC14-OSC32_IN.GPIO_Label=A0_A0
PB10.GPIOParameters=GPIO_Label
PC15-OSC32_OUT.GPIOParameters=GPIO_Label
PA4.GPIO_Label=D4
PA3.Signal=GPIO_Output
PA6.GPIOParameters=GPIO_Label
PB8.GPIOParameters=GPIO_Label
PB9.GPIO_Label=WR_A1
PA10.Mode=Asynchronous
PB11.GPIO_Label=A0_V1
PC13-TAMPER-RTC.Signal=GPIO_Output
PA11.GPIO_Label=ROT_A_A
PD0-OSC_IN.Signal=GPIO_Output
PC14-OSC32_IN.Signal=GPIO_Output
PB13.GPIO_ModeDefaultEXTI=GPIO_MODE_IT_RISING_FALLING
PA12.GPIO_Label=ROT_A_B
PA0-WKUP.GPIO_Label=D0
PA0-WKUP.Signal=GPIO_Output
PB9.GPIOParameters=GPIO_Label
PA13.Signal=SYS_JTMS-SWDIO
PB8.GPIO_Label=RELAY
PA9.Mode=Asynchronous
PA8.GPIO_Label=ROT_A_S
PB10.GPIO_Label=WR_V1
PB2.GPIOParameters=GPIO_Label
PA9.Signal=USART1_TX
PB11.GPIOParameters=GPIO_Label
PC15-OSC32_OUT.Signal=GPIO_Output
PA1.Signal=GPIO_Output
PB10.Signal=GPIO_Output
PB14.Signal=GPIO_Input
PA5.Signal=GPIO_Output
board=custom
PD0-OSC_IN.GPIO_Label=A0_A1
PC13-TAMPER-RTC.GPIO_Label=WR_A0
PB15.GPIO_Label=ROT_V_S
PA1.GPIO_Label=D1
PA4.GPIOParameters=GPIO_Label
PB15.GPIOParameters=GPIO_Label
PA13.Mode=Serial_Wire
Mcu.Name=STM32F100C(4-6)Tx
PD0-OSC_IN.GPIOParameters=GPIO_Label
PA2.Signal=GPIO_Output
PA4.Signal=GPIO_Output
RCC.SYSCLKFreq_VALUE=24000000
PA5.GPIO_Label=D5
PB7.Mode=I2C
PA11.Signal=GPXTI11
PA14.Signal=SYS_JTCK-SWCLK
PB2.GPIO_Label=A1_V0
PB8.Signal=GPIO_Output
PA11.GPIO_ModeDefaultEXTI=GPIO_MODE_IT_RISING_FALLING
PB0.Signal=GPIO_Output
PB12.GPIOParameters=GPIO_Label
PB12.Signal=GPIO_Output
PA3.GPIO_Label=D3
PB1.GPIOParameters=GPIO_Label

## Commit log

2021-02-28 Initial checkin
2021-09-05 fixed bugs in PCB, added frontpanel, added SW for frontpanel
